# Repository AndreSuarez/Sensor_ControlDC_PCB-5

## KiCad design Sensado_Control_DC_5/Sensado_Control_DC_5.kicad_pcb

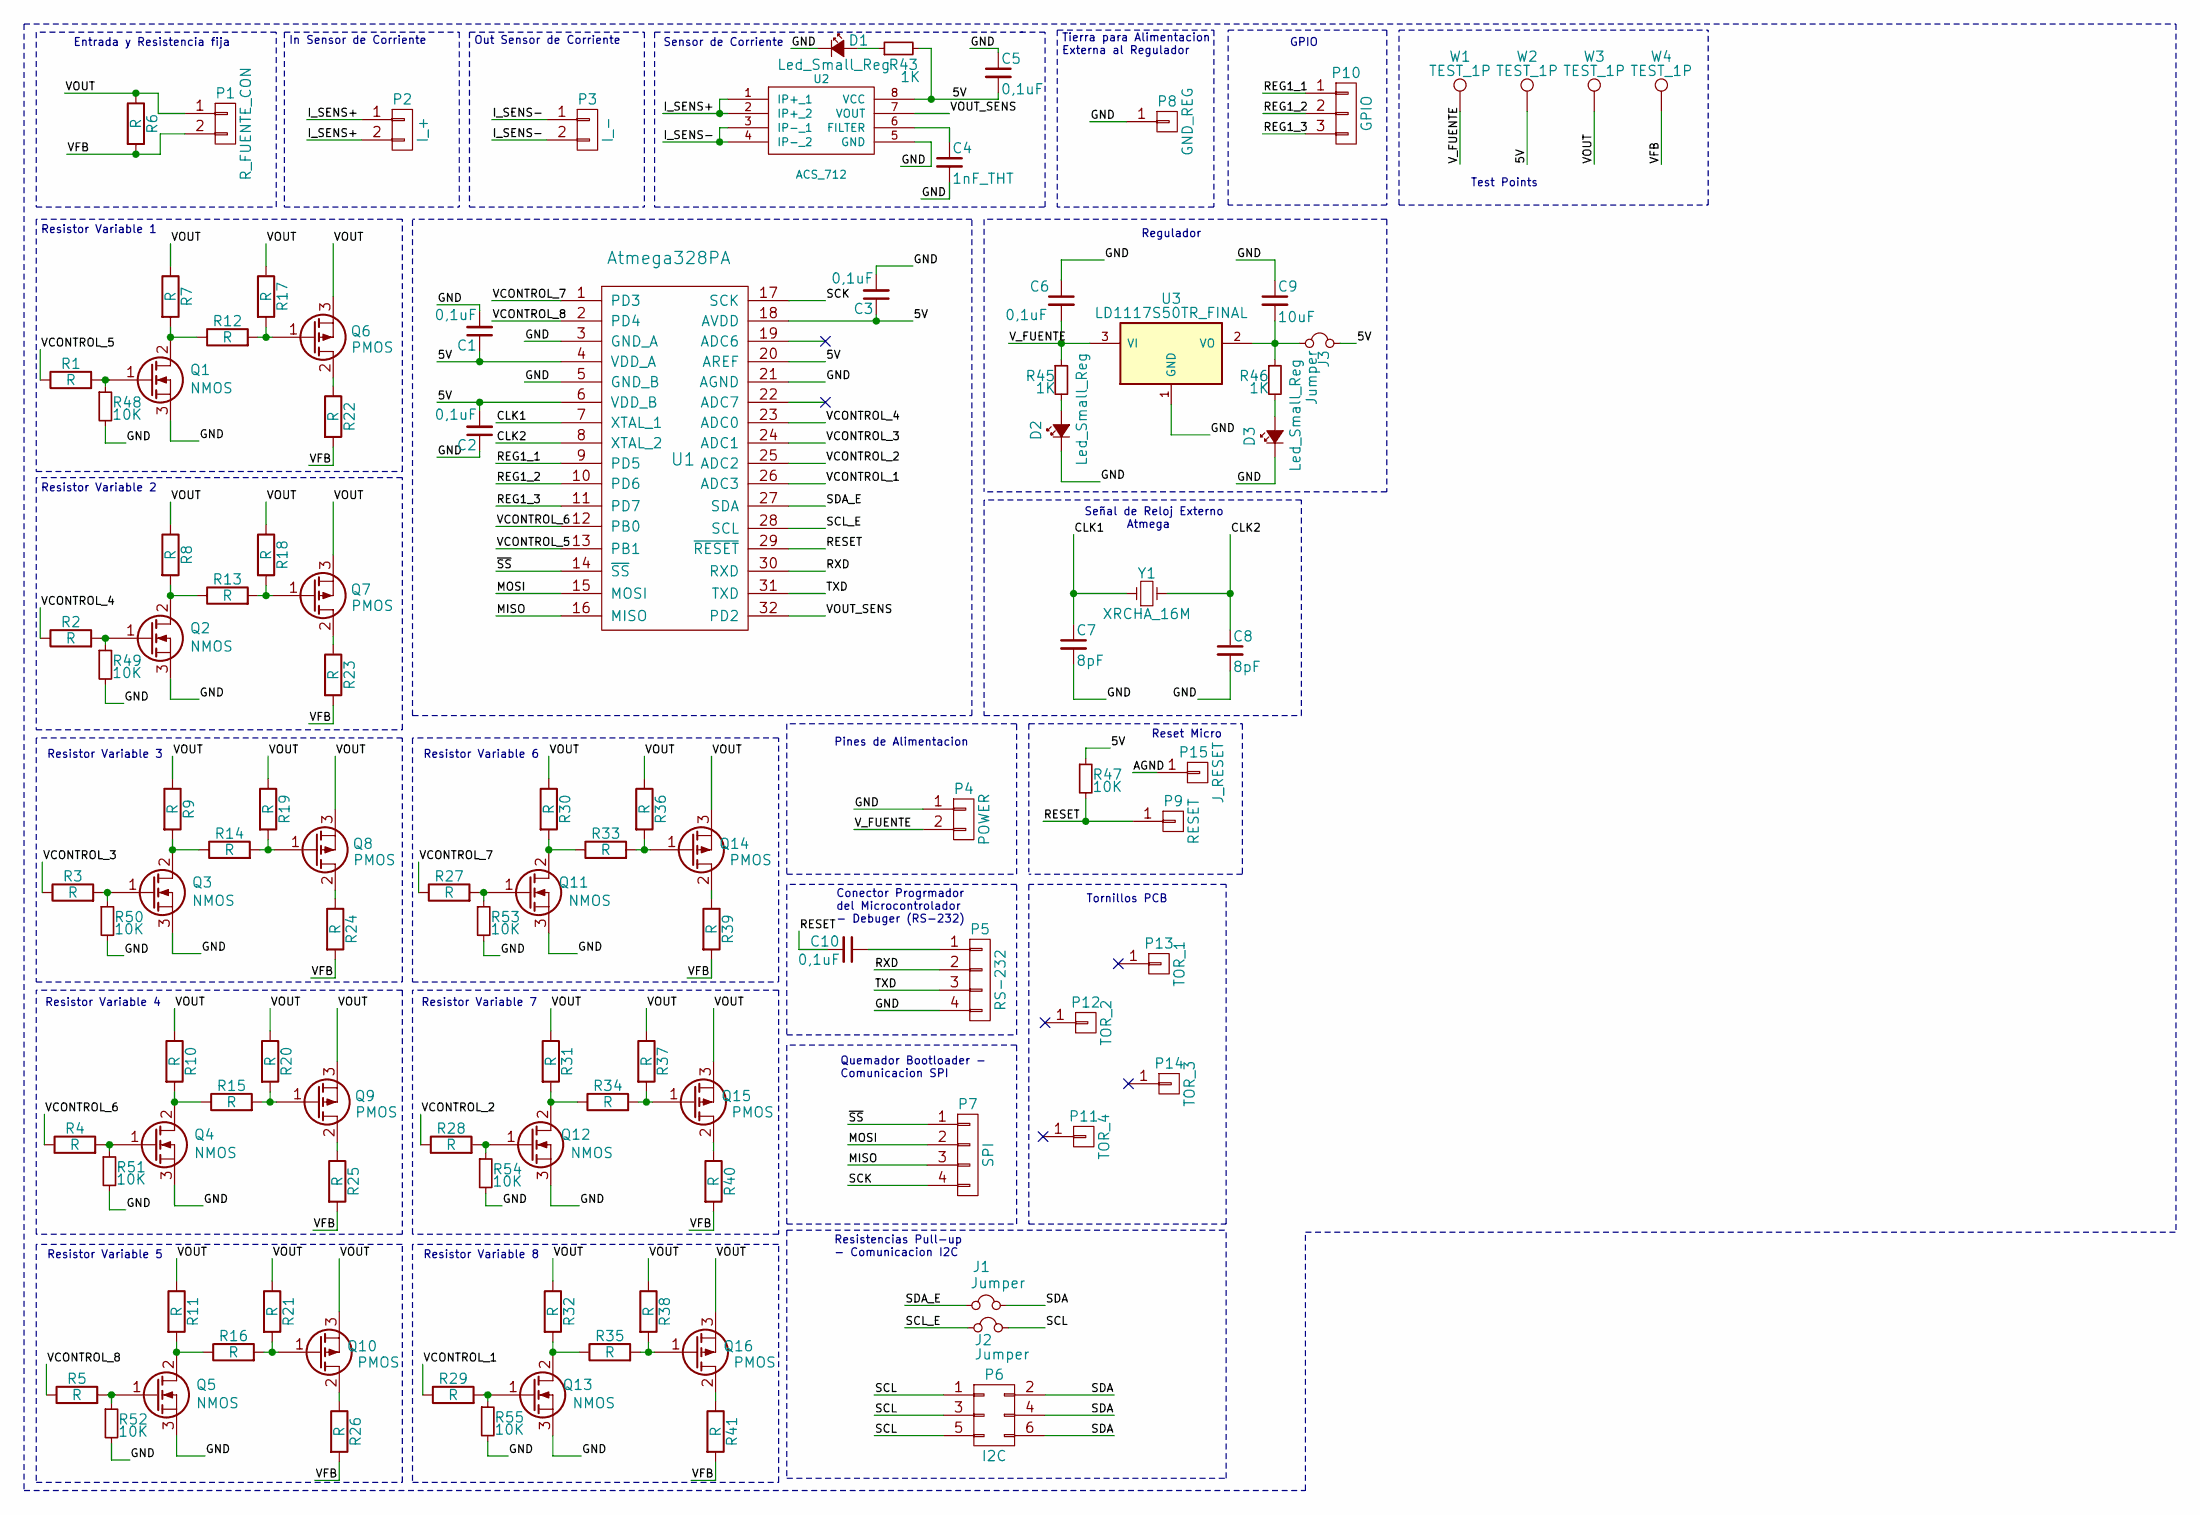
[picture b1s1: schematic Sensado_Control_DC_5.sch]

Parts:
C1, C2, C3, C5, C6, C10: 0,1uF; C_0805_HandSoldering
C4: 1nF_THT; C_Disc_D5.0mm_W2.5mm_P2.50mm
C7, C8: 8pF; C_0402
C9: 10uF; C_0805_HandSoldering
D1, D2, D3: Led_Small_Reg; LED_0805
J1, J2, J3: Jumper; Pin_Header_Straight_1x02_Pitch2.54mm
P1: R_FUENTE_CON; Socket_MOLEX-KK-RM3-96mm_Lock_2pin_straight
P2: I_+; Socket_MOLEX-KK-RM3-96mm_Lock_2pin_straight
P3: I_-; Socket_MOLEX-KK-RM3-96mm_Lock_2pin_straight
P4: POWER; Socket_MOLEX-KK-RM3-96mm_Lock_2pin_straight
P5: RS-232; Socket_Strip_Straight_1x04_Pitch2.54mm
P6: I2C; Socket_Strip_Straight_2x03_Pitch2.54mm
P7: SPI; Socket_Strip_Straight_1x04_Pitch2.54mm
P8: GND_REG; Socket_Strip_Straight_1x01_Pitch2.54mm
P9: RESET; Socket_Strip_Straight_1x01_Pitch2.54mm
P10: GPIO; Socket_Strip_Straight_1x03_Pitch2.54mm
P11: TOR_4; MountingHole_3.2mm_M3_Pad_Via
P12: TOR_2; MountingHole_3.2mm_M3_Pad_Via
P13: TOR_1; MountingHole_3.2mm_M3_Pad_Via
P14: TOR_3; MountingHole_3.2mm_M3_Pad_Via
P15: J_RESET; Socket_Strip_Straight_1x01_Pitch2.54mm
Q1, Q2, Q3, Q4, Q5, Q11, Q12, Q13: NMOS; TO-220_Vertical
Q6, Q7, Q8, Q9, Q10, Q14, Q15, Q16: PMOS; TO-220_Vertical
R1, R2, R3, R4, R5, R6, R7, R8, R9, R10, R11, R12, R13, R14, R15, R16, R17, R18, R19, R20, R21, R22, R23, R24, R25, R26, R27, R28, R29, R30, R31, R32, R33, R34, R35, R36, R37, R38, R39, R40, R41: R; R_Axial_DIN0207_L6.3mm_D2.5mm_P7.62mm_Horizontal
R43, R45, R46: 1K; R_0805_HandSoldering
R47, R48, R49, R50, R51, R52, R53, R54, R55: 10K; R_0805_HandSoldering
U1: Atmega328PA; TQFP-32_7x7mm_Pitch0.8mm
U2: ACS_712; SOIC-8_3.9x4.9mm_Pitch1.27mm
U3: LD1117S50TR_FINAL; SOT-223
W1, W2, W3, W4: TEST_1P; Measurement_Point_Round-TH_Small
Y1: XRCHA_16M; Crystal_SMD_XRCHA_Murata_Serie_W2,5mm_L2,0mm

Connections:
/5V: C1.1, C2.2, C3.1, C5.2, J3.1, R43.2, R47.1, U1.4 (VDD_A), U1.6 (VDD_B), U1.18 (AVDD), U1.20 (AREF), U2.8 (VCC), W2.1
/AGND: P15.1
/CLK1: C7.1, U1.7 (XTAL_1), Y1.1
/CLK2: C8.1, U1.8 (XTAL_2), Y1.2
/GND: C1.2, C2.1, C3.2, C4.2, C5.1, C6.1, C7.2, C8.2, C9.1, D1.1 (K), D2.1 (K), D3.1 (K), P4.1, P5.4, P8.1, Q1.3 (S), Q2.3 (S), Q3.3 (S), Q4.3 (S), Q5.3 (S), Q11.3 (S), Q12.3 (S), Q13.3 (S), R48.2, R49.2, R50.2, R51.2, R52.2, R53.2, R54.2, R55.2, U1.3 (GND_A), U1.5 (GND_B), U1.21 (AGND), U2.5 (GND), U3.1 (GND)
/I_SENS+: P2.1, P2.2, U2.1 (IP+_1), U2.2 (IP+_2), U2.~ (IP+_1)
/I_SENS-: P3.1, P3.2, U2.3 (IP-_1), U2.4 (IP-_2)
/MISO: P7.3, U1.16 (MISO)
/MOSI: P7.2, U1.15 (MOSI)
/REG1_1: P10.1, U1.9 (PD5)
/REG1_2: P10.2, U1.10 (PD6)
/REG1_3: P10.3, U1.11 (PD7)
/RESET: C10.2, P9.1, R47.2, U1.29 (~RESET)
/RXD: P5.2, U1.30 (RXD)
/SCK: P7.4, U1.17 (SCK)
/SCL: J2.1, P6.1, P6.3, P6.5
/SCL_E: J2.2, U1.28 (SCL)
/SDA: J1.1, P6.2, P6.4, P6.6
/SDA_E: J1.2, U1.27 (SDA)
/TXD: P5.3, U1.31 (TXD)
/VCONTROL_1: R29.1, U1.26 (ADC3)
/VCONTROL_2: R28.1, U1.25 (ADC2)
/VCONTROL_3: R3.1, U1.24 (ADC1)
/VCONTROL_4: R2.1, U1.23 (ADC0)
/VCONTROL_5: R1.1, U1.13 (PB1)
/VCONTROL_6: R4.1, U1.12 (PB0)
/VCONTROL_7: R27.1, U1.1 (PD3)
/VCONTROL_8: R5.1, U1.2 (PD4)
/VFB: P1.2, R6.2, R22.2, R23.2, R24.2, R25.2, R26.2, R39.2, R40.2, R41.2, W4.1
/VOUT: P1.1, Q6.3 (S), Q7.3 (S), Q8.3 (S), Q9.3 (S), Q10.3 (S), Q14.3 (S), Q15.3 (S), Q16.3 (S), R6.1, R7.1, R8.1, R9.1, R10.1, R11.1, R17.1, R18.1, R19.1, R20.1, R21.1, R30.1, R31.1, R32.1, R36.1, R37.1, R38.1, W3.1
/VOUT_SENS: U1.32 (PD2), U2.7 (VOUT)
/V_FUENTE: C6.2, P4.2, R45.1, U3.3 (VI), W1.1
/~SS: P7.1, U1.14 (~SS)
unnamed: C4.1, U2.6 (FILTER)
unnamed: C9.2, J3.2, R46.1, U3.2 (VO)
unnamed: C10.1, P5.1
unnamed: D1.2 (A), R43.1
unnamed: D2.2 (A), R45.2
unnamed: D3.2 (A), R46.2
unnamed: Q1.1 (G), R1.2, R48.1
unnamed: Q1.2 (D), R7.2, R12.1
unnamed: Q2.1 (G), R2.2, R49.1
unnamed: Q2.2 (D), R8.2, R13.1
unnamed: Q3.1 (G), R3.2, R50.1
unnamed: Q3.2 (D), R9.2, R14.1
unnamed: Q4.1 (G), R4.2, R51.1
unnamed: Q4.2 (D), R10.2, R15.1
unnamed: Q5.1 (G), R5.2, R52.1
unnamed: Q5.2 (D), R11.2, R16.1
unnamed: Q6.1 (G), R12.2, R17.2
unnamed: Q6.2 (D), R22.1
unnamed: Q7.1 (G), R13.2, R18.2
unnamed: Q7.2 (D), R23.1
unnamed: Q8.1 (G), R14.2, R19.2
unnamed: Q8.2 (D), R24.1
unnamed: Q9.1 (G), R15.2, R20.2
unnamed: Q9.2 (D), R25.1
unnamed: Q10.1 (G), R16.2, R21.2
unnamed: Q10.2 (D), R26.1
unnamed: Q11.1 (G), R27.2, R53.1
unnamed: Q11.2 (D), R30.2, R33.1
unnamed: Q12.1 (G), R28.2, R54.1
unnamed: Q12.2 (D), R31.2, R34.1
unnamed: Q13.1 (G), R29.2, R55.1
unnamed: Q13.2 (D), R32.2, R35.1
unnamed: Q14.1 (G), R33.2, R36.2
unnamed: Q14.2 (D), R39.1
unnamed: Q15.1 (G), R34.2, R37.2
unnamed: Q15.2 (D), R40.1
unnamed: Q16.1 (G), R35.2, R38.2
unnamed: Q16.2 (D), R41.1

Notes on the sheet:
Entrada y Resistencia fija
Resistor Variable 1
In Sensor de Corriente
Sensor de Corriente
Out Sensor de Corriente
Pines de Alimentacion
Conector Progrmador del Microcontrolador - Debuger (RS-232)
Quemador Bootloader - Comunicacion SPI
Resistencias Pull-up - Comunicacion I2C
Regulador
Tierra para Alimentacion Externa al Regulador
Señal de Reloj Externo Atmega
Resistor Variable 2
Resistor Variable 3
Resistor Variable 4
Resistor Variable 5
Resistor Variable 6
Resistor Variable 7
Resistor Variable 8
GPIO
Reset Micro
Tornillos PCB
Test Points

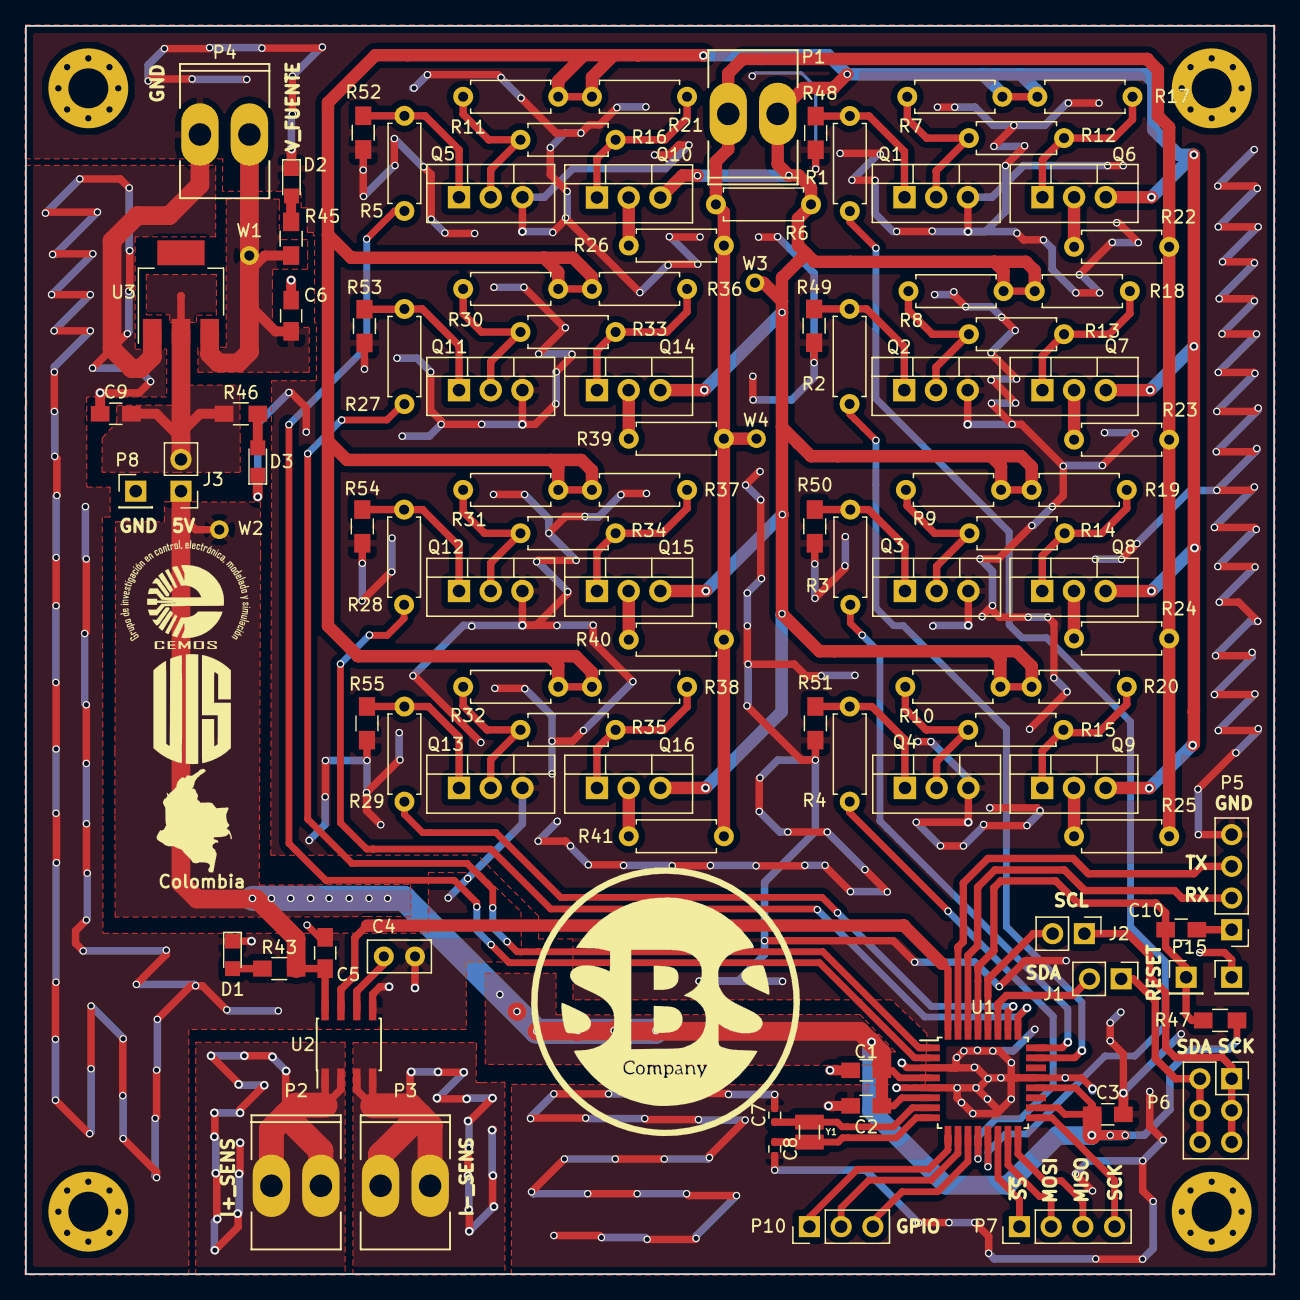
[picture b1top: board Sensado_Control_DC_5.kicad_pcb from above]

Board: 2 copper layers, 100.0 x 100.0 mm, 108 parts (0 on the bottom side), 70 nets.

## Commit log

2017-09-28 Creacion Proyecto Sensor y Control Dc
2017-09-30 Control DC, y Micro placa 5
2017-10-01 Version avanzada PCB
2017-10-01 Isletas y clock añadido a la PCB
2017-10-02 PCB version final preliminar
2017-10-02 PCB mejorada
2017-10-02 PCB planos del sensor de corriente actualizados
2017-10-02 Puertos I2C mejorados
2017-10-02 Regletas con nobres definidos para sus respectivos pines
2017-10-03 Vias para el sensor de corriente, PCB version final
2017-10-03 Gerber generado
2017-10-03 Version PCB con tornillos incluidos
2017-10-04 Version para placa
2017-10-04 Capacitor DTR, Jumper Reset
2017-10-05 Logos y Nombre de Placa
2017-10-05 Vias para toda PCB
2017-10-05 Archivo .zip actualizado de Gerbers
2017-10-05 Resistencias de pull up quitadas
2017-10-05 Capacitor del Cristal 0402 cambiados
2017-10-05 Archivo .zip Gerber actualizado
2017-10-05 Nombre de Colombia añadido
